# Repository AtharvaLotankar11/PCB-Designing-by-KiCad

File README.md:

<div align="center">

# 🎨 PCB Designing with KiCad

### *Transforming Circuit Ideas into Professional PCBs*

</div>

---

## 📖 About KiCad

**KiCad** is a powerful, free, and open-source Electronic Design Automation (EDA) suite trusted by professionals and hobbyists worldwide. It provides a complete workflow for hardware development:

- 🖊️ **Schematic Design** - Draw and organize complex circuit diagrams
- 🔧 **PCB Layout** - Route multi-layer boards with precision
- 📦 **Manufacturing Files** - Generate Gerber files ready for fabrication
- 🎨 **3D Visualization** - Preview your board before production
- 📚 **Extensive Libraries** - Access thousands of component footprints

Whether you're prototyping a hobby project or developing a commercial product, KiCad equips you with everything needed to bring your electronic designs to life.

---

## 🎹 Featured Projects

### 🎵 Touch Piano

<div align="center">

</div>

A **touch-based musical instrument** powered by a microcontroller that transforms capacitive touch into musical notes.

**Key Features:**
- Touch-sensitive pads with large copper pours
- Microcontroller integration (ATmega/ESP32)
- Piezo speaker output
- Compact, interactive design

**Design Highlights:**
- Careful routing to minimize analog interference
- Strategic component placement using 3D viewer
- Perfect example of interactive electronics prototyping

---

### ⚡ Buck Converter

<div align="center">

</div>

An efficient **DC-DC step-down converter** for voltage regulation in battery-powered applications.

**Key Features:**
- Switching regulator IC with external passives
- Optimized power trace routing
- Thermal relief considerations
- DRC-verified layout

**Design Highlights:**
- Strategic placement of inductors and capacitors
- Noise reduction through proper layout
- Production-ready power supply solution

---

## 🚀 Why KiCad?

<div align="center">

| Feature | Benefit |
|---------|---------|
| 🆓 **Free & Open Source** | No licensing costs, full access to source code |
| 🌍 **Cross-Platform** | Works on Windows, macOS, and Linux |
| 🔄 **Active Development** | Regular updates and community support |
| 🧩 **Plugin Ecosystem** | Extend functionality with custom tools |
| 📐 **Professional Grade** | Used in commercial and industrial applications |

</div>

---

## 💡 Getting Started

1. **Download KiCad** from [kicad.org](https://www.kicad.org/)
2. **Explore the projects** in this repository
3. **Open the `.kicad_pro` files** to view schematics and PCB layouts
4. **Learn and iterate** on your own designs

---

## 📂 Repository Structure

```
📦 PCB-Designs
 ┣ 📁 BUCK CONVERTER FINAL/     # Buck converter project files
 ┣ 📁 piano wkshp/               # Touch piano project files
 ┣ 🖼️ buck.gif                   # Buck converter preview
 ┣ 🖼️ piano.gif                  # Piano project preview
 ┣ 🖼️ intro.gif                  # KiCad introduction
 ┗ 📄 README.md                  # You are here!
```

---

## 🎯 Conclusion

KiCad proves to be an **exceptional tool** for PCB design across diverse electronics projects. From musical instruments to power electronics, it supports the entire workflow with **precision and flexibility**.

This repository showcases real-world applications and demonstrates how **accessible hardware design** has become. Whether you're a beginner or experienced engineer, KiCad helps you transform ideas into professional-grade PCBs with confidence.

---

<div align="center">

### ⭐ Star this repo if you find it helpful!

**Made with ❤️ using KiCad**

</div>

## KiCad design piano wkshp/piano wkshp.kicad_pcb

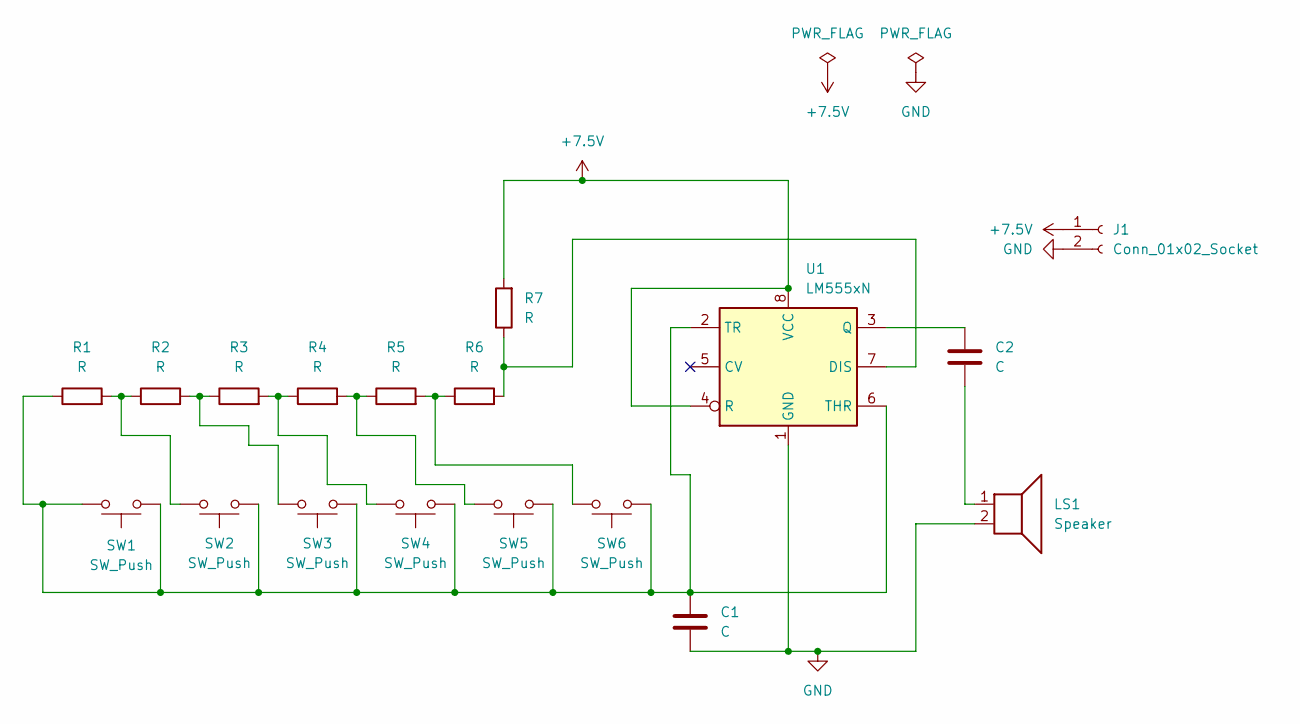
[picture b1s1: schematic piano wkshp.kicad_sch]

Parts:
C1, C2: C; C_Disc_D5.0mm_W2.5mm_P5.00mm
J1: Conn_01x02_Socket; TerminalBlock_Phoenix_MKDS-1,5-2_1x02_P5.00mm_Horizontal
LS1: Speaker; TerminalBlock_Phoenix_MKDS-1,5-2_1x02_P5.00mm_Horizontal
R1, R2, R3, R4, R5, R6, R7: R; R_Axial_DIN0207_L6.3mm_D2.5mm_P10.16mm_Horizontal
SW1, SW2, SW3, SW4, SW5, SW6: SW_Push; SW_PUSH_6mm_H8mm
U1: LM555xN; DIP-8_W7.62mm

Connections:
+7.5V: J1.1, R7.2, U1.4 (R), U1.8 (VCC)
GND: C1.2, J1.2, LS1.2, U1.1 (GND)
unnamed: C2.2, LS1.1
unnamed: R1.2, R2.1, SW2.2
unnamed: R2.2, R3.1, SW3.2
unnamed: R3.2, R4.1, SW4.2
unnamed: R4.2, R5.1, SW5.2
unnamed: R5.2, R6.1, SW6.2
unnamed: R6.2, R7.1, U1.7 (DIS)
unnamed: C2.1, U1.3 (Q)
unnamed: C1.1, R1.1, SW1.1, SW1.2, SW2.1, SW3.1, SW4.1, SW5.1, SW6.1, U1.2 (TR), U1.6 (THR)

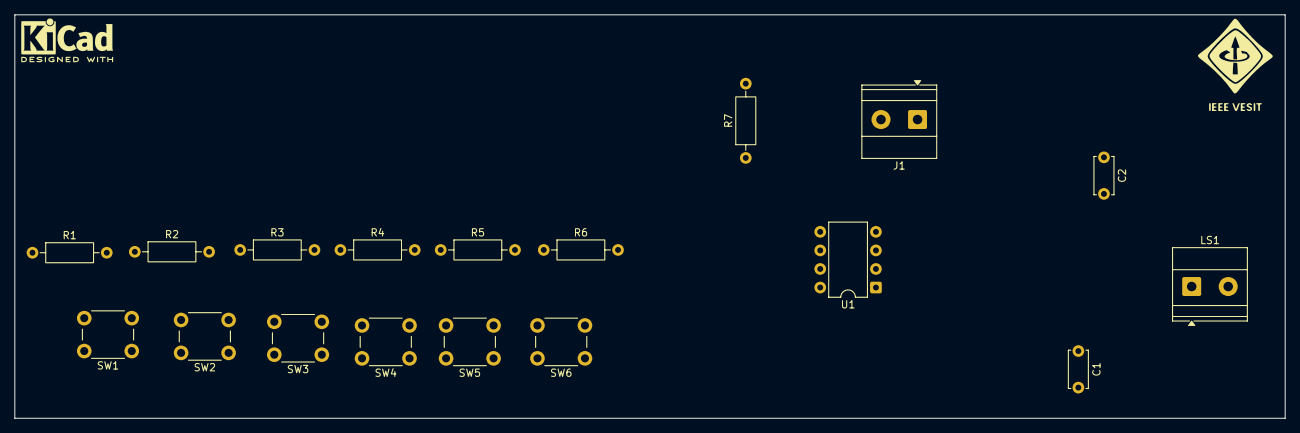
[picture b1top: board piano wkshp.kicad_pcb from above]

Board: 2 copper layers, 173.8 x 55.2 mm, 18 parts (0 on the bottom side), 11 nets.

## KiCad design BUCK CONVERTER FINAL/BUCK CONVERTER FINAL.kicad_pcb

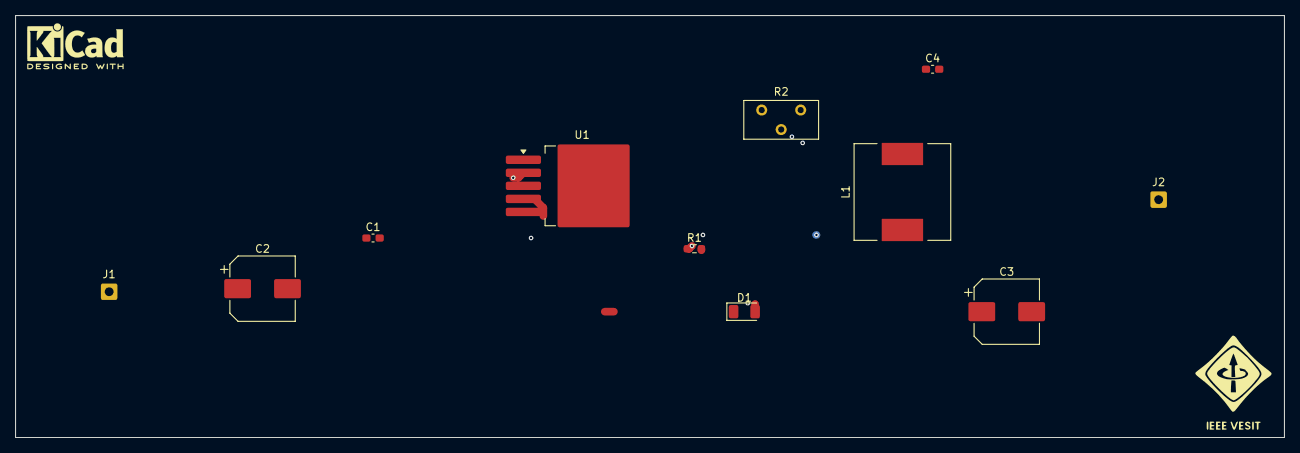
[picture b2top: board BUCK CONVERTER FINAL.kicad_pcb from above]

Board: 2 copper layers, 165.4 x 55.0 mm, 11 parts (0 on the bottom side), 5 nets.

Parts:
C1, C4: 100nF; C_0603_1608Metric_Pad1.08x0.95mm_HandSolder
C2: 100uF; CP_Elec_8x10
C3: 220uF; CP_Elec_8x10
D1: 1N5822; D_1206_3216Metric
J1, J2: Screw_Terminal_01x02; SolderWire-0.5sqmm_1x01_D0.9mm_OD2.1mm
L1: 470m; L_12x12mm_H8mm
R1: 330; R_0603_1608Metric_Pad0.98x0.95mm_HandSolder
R2: 103; Potentiometer_Bourns_3296Y_Vertical
U1: LM2596S-ADJ; TO-263-5_TabPin3

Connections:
GND: C1.2, C2.2, C3.2, D1.2 (A), R1.2, U1.3 (GND), U1.5 (~ON/OFF)
unnamed: D1.1 (K), L1.1, U1.2 (OUT)
unnamed: C1.1, C2.1, J1.1, U1.1 (VIN)
unnamed: C3.1, C4.2, J2.1, L1.2, R2.2
unnamed: C4.1, R1.1, R2.1, U1.4 (FB)

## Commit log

2025-07-19 PCB-KiCad
2025-07-19 CreateREADME.md
2025-11-04 Enhance README.md with attractive and clean UI design

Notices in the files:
README.md:
License: Open Source
